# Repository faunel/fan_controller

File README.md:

English | [Українська](README.uk.md)

# PWM Fan Controller Board

A control board for regulating fan speed using PWM (Pulse-Width Modulation).

## Overview

This board is designed to control up to four fans based on temperature readings from up to four NTC thermistors.  
It is intended, in particular, for use with hybrid inverters and includes an inverter fan emulation mode.

- Total output current: up to **5 A**, sufficient with a large margin for typical fans
- Temperature sensor type: **NTC 10 kΩ**
- Up to **4 fans** supported
- Up to **4 temperature sensors** supported
- **4 fan speed levels** depending on temperature
- **1 additional default speed** (used when temperature is below the first level)

## Fan–Sensor Mapping

Fan control logic is configurable in the menu:

- Any sensor can control any fan or group of fans
- All combinations are allowed

Examples:

- One sensor controls all 4 fans
- Two sensors:  
  - Sensor 1 controls fans 1–2  
  - Sensor 2 controls fans 3–4
- One sensor controls a single fan, another sensor controls the remaining three, etc.

The main menu displays for each fan/sensor:

- Temperature
- Fan speed (RPM)
- Current speed level (step)

## Hybrid Inverter Integration

The board is designed to work with a hybrid inverter and supports an **inverter fan emulation mode**.

- If the configuration allows the fans to be stopped (note: not all fans support full stop),
  the inverter will **not** generate a “fan stopped” error.
- Emulation is implemented by generating pulses at **300 Hz** on the signal (yellow) wire
  of the fan connector where the inverter’s original fan would normally be connected.

This corresponds to **9000 RPM** of the fan:

- 2 pulses per revolution  
- Formula: `300 / 2 * 60 = 9000`

### Fan Fault Handling

If the configuration requires a fan to rotate but it does not (for example):

- the connector is unplugged,
- the fan is blocked by a foreign object,
- the fan is defective,

then the inverter will detect an error and shut down until the cause is eliminated.  
This behaviour is intentional to prevent inverter overheating.

## Firmware / Development

### Flashing the firmware

```bash
cargo flash --chip stm32f411ceu6 --release
```

### Build and run with active terminal output

```bash
cargo run --release
```

### Build and detach from terminal

```bash
cargo embed --release
```

### Convert to HEX file

```bash
cargo-objcopy target/thumbv7em-none-eabihf/release/two --release -- -O ihex two.hex
```

### Disassembly

```bash
cargo objdump --bin two --release -- --disassemble --no-show-raw-insn --print-imm-hex
```

### Start OpenOCD

```bash
openocd -f interface/stlink.cfg -f target/stm32f4x.cfg
```

### Check program size

```bash
cargo size --bin fan_controller --release -- -A
```

## Memory Layout

### Program memory (Flash, base address: `0x08000000`)

- `.vector_table` – interrupt vector table, usually at the beginning of memory, containing addresses of interrupt handlers
- `.text` – section with program machine code (instructions)
- `.rodata` – section for constant, read-only data

### RAM (base address: `0x20000000`)

- `.data` – global and static variables initialized to specific values
- `.bss` – global and static variables initialized to zero
- `.uninit` – variables that are not initialized at program start

### Sections not included in the final binary / not critical for runtime

- `.gnu.sgstubs` – may contain special GNU-specific stubs
- `.ARM.attributes` – ARM-architecture-specific attributes
- `.comment` – comments or metadata
- `.defmt` – data for formatted output (e.g., for the `defmt` library)

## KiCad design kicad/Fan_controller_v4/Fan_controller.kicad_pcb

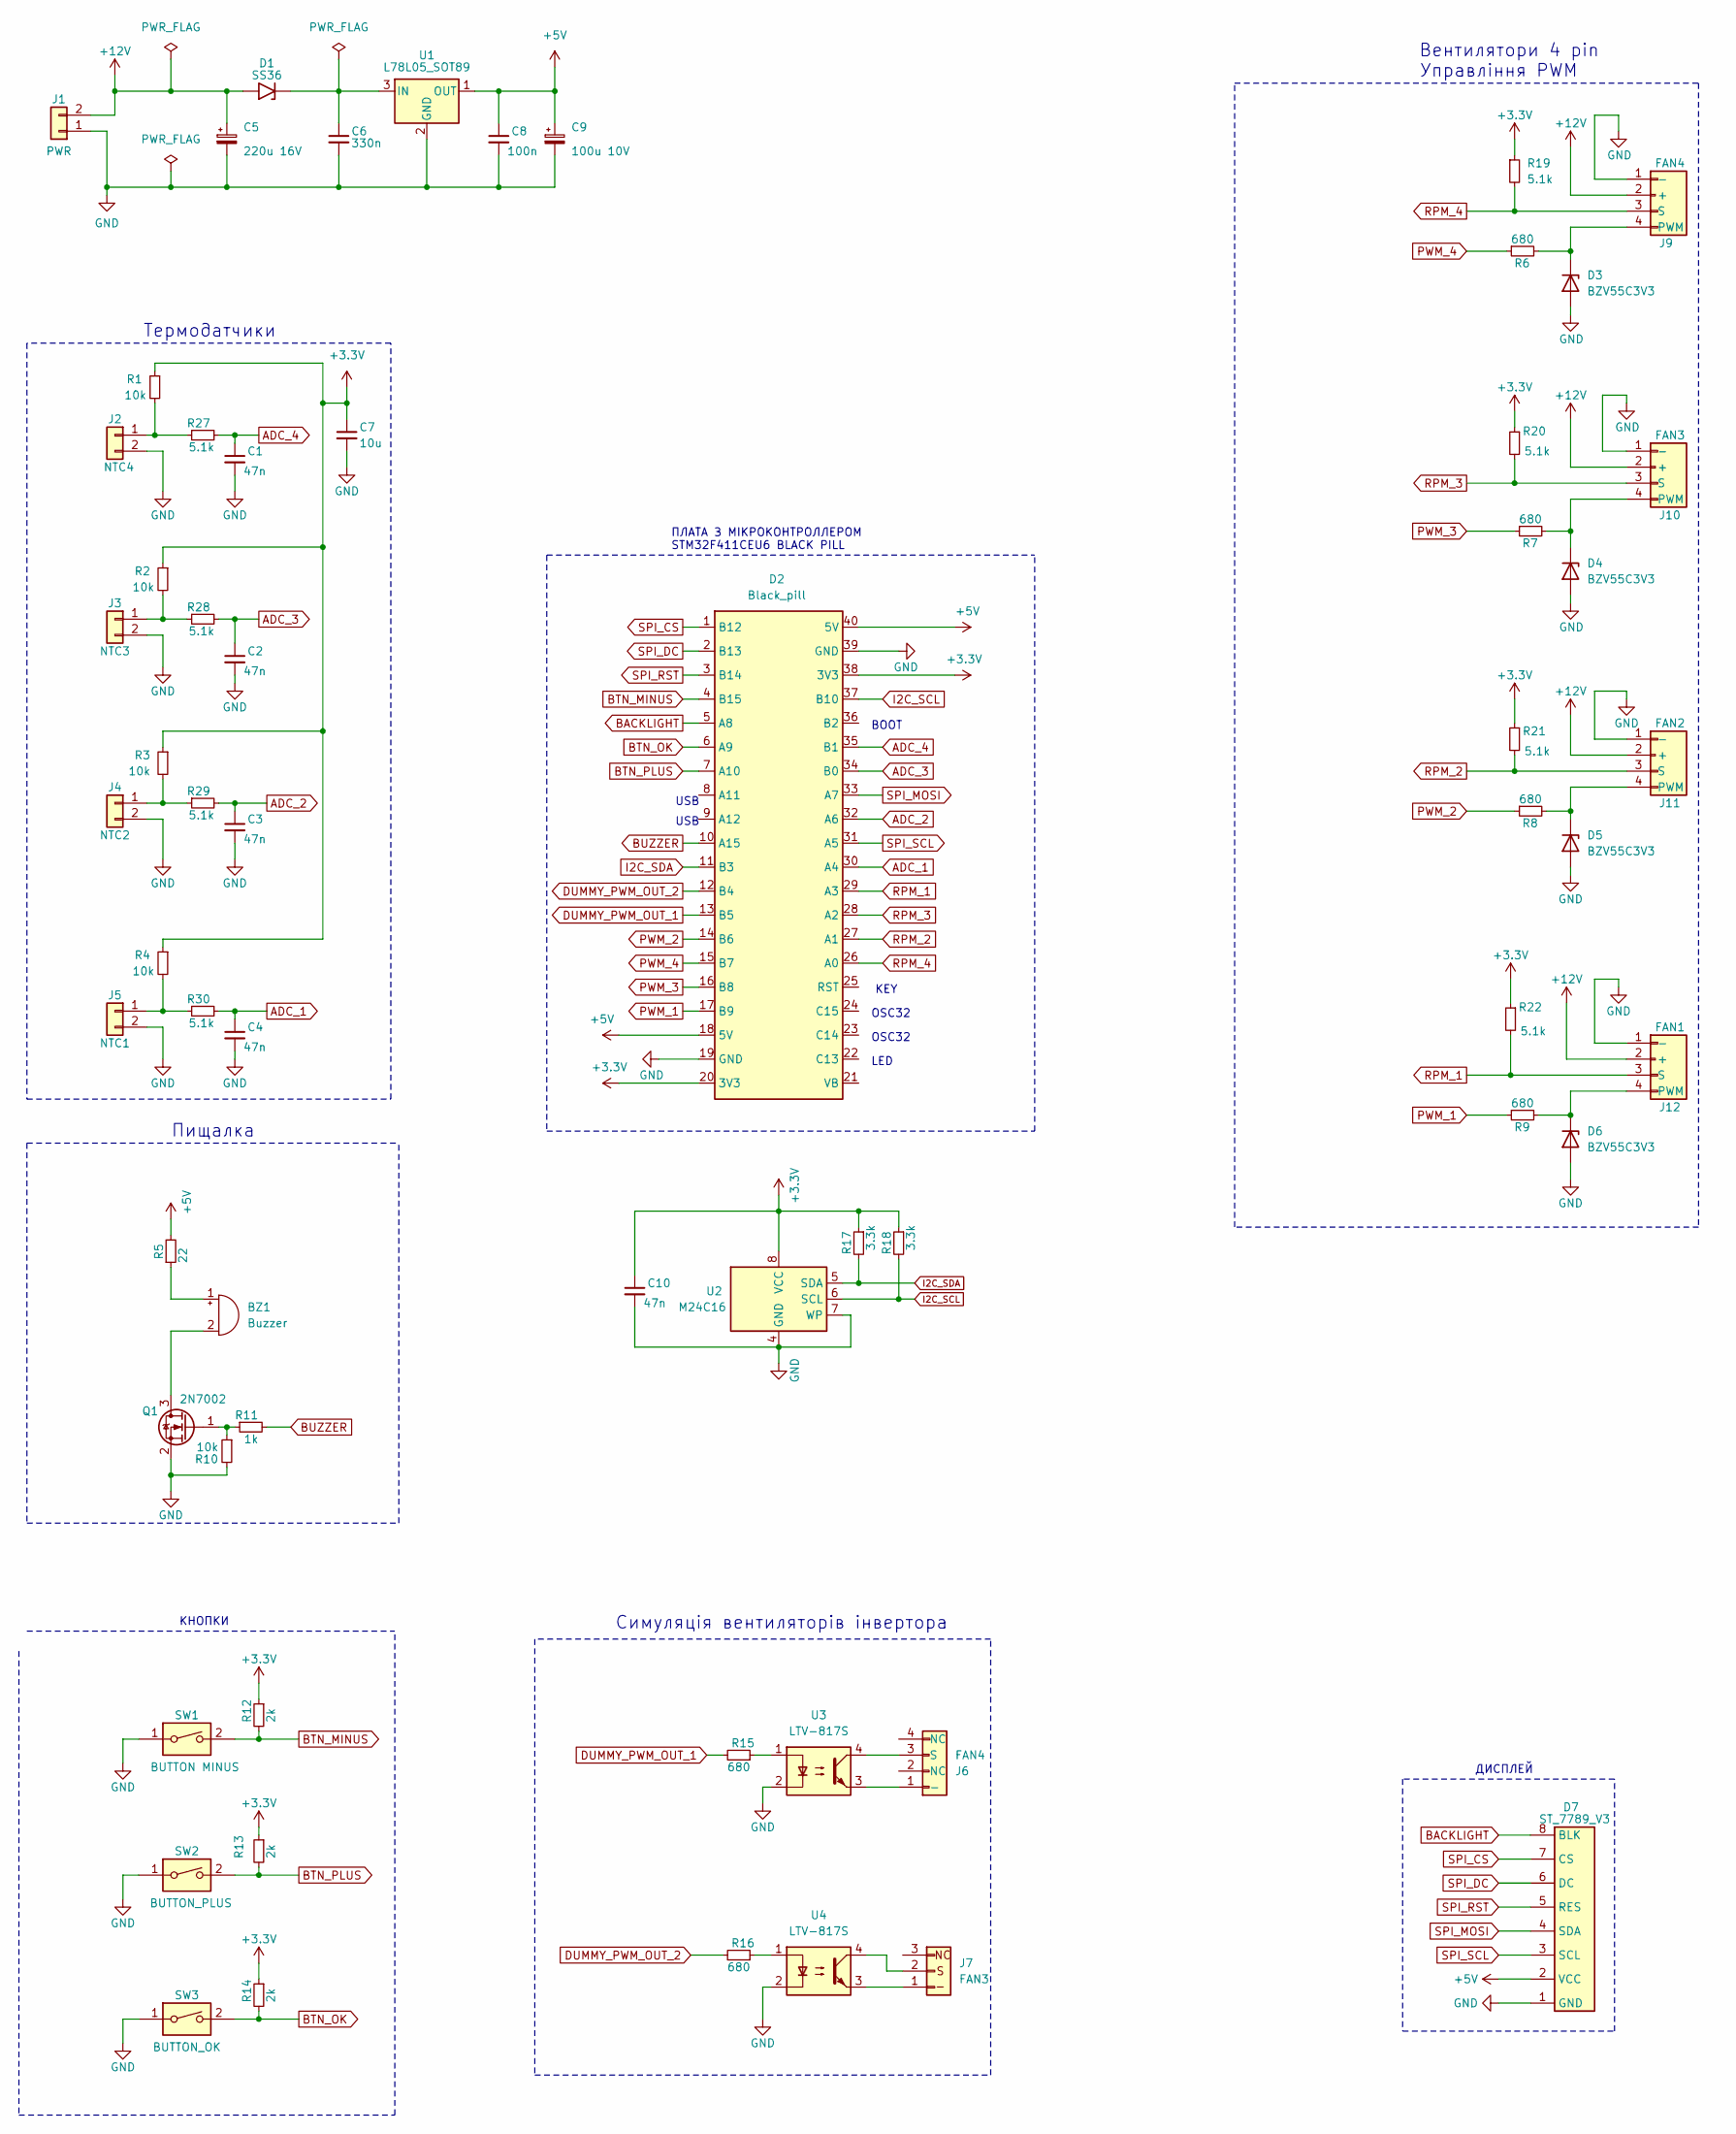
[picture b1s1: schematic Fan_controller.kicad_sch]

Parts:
BZ1: Buzzer; Buzzer_12x9.5RM7.6
C1, C2, C3, C4, C10: 47n; C_0805_2012Metric_Pad1.18x1.45mm_HandSolder
C5: 220u 16V; CP_Elec_6.3x7.7
C6: 330n; C_0805_2012Metric_Pad1.18x1.45mm_HandSolder
C7: 10u; C_0805_2012Metric_Pad1.18x1.45mm_HandSolder
C8: 100n; C_0805_2012Metric_Pad1.18x1.45mm_HandSolder
C9: 100u 10V; CP_Elec_5x5.4
D1: SS36; D_SMA-SMB_Universal_Handsoldering
D2: Black_pill
D3, D4, D5, D6: BZV55C3V3; D_SOD-123
D7: ST_7789_V3
J1: PWR; TerminalBlock_MetzConnect_Type094_RT03502HBLU_1x02_P5.00mm_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
J2: NTC4; JST_XH_B2B-XH-A_1x02_P2.50mm_Vertical
J3: NTC3; JST_XH_B2B-XH-A_1x02_P2.50mm_Vertical
J4: NTC2; JST_XH_B2B-XH-A_1x02_P2.50mm_Vertical
J5: NTC1; JST_XH_B2B-XH-A_1x02_P2.50mm_Vertical
J6: FAN4; JST_XH_B4B-XH-A_1x04_P2.50mm_Vertical
J7: FAN3; JST_XH_B3B-XH-A_1x03_P2.50mm_Vertical
J9: FAN4; FanPinHeader_1x04_P2.54mm_Vertical
J10: FAN3; FanPinHeader_1x04_P2.54mm_Vertical
J11: FAN2; FanPinHeader_1x04_P2.54mm_Vertical
J12: FAN1; FanPinHeader_1x04_P2.54mm_Vertical
Q1: 2N7002; SOT-23
R1, R2, R3, R4, R10: 10k; R_0805_2012Metric_Pad1.20x1.40mm_HandSolder
R5: 22; R_0805_2012Metric_Pad1.20x1.40mm_HandSolder
R6, R7, R8, R9, R15, R16: 680; R_0805_2012Metric_Pad1.20x1.40mm_HandSolder
R11: 1k; R_0805_2012Metric_Pad1.20x1.40mm_HandSolder
R12, R13, R14: 2k; R_0805_2012Metric_Pad1.20x1.40mm_HandSolder
R17, R18: 3.3k; R_0805_2012Metric_Pad1.20x1.40mm_HandSolder
R19, R20, R21, R22, R27, R28, R29, R30: 5.1k; R_0805_2012Metric_Pad1.20x1.40mm_HandSolder
SW1: BUTTON MINUS; SW_PUSH-12mm
SW2: BUTTON_PLUS; SW_PUSH-12mm
SW3: BUTTON_OK; SW_PUSH-12mm
U1: L78L05_SOT89; SOT-89-3
U2: M24C16; SOIC-8_3.9x4.9mm_P1.27mm
U3, U4: LTV-817S; SMDIP-4_W9.53mm

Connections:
+3.3V: C7.1, C10.1, D2.20 (3V3), D2.38 (3V3), R1.1, R2.1, R3.1, R4.1, R12.1, R13.1, R14.1, R17.1, R18.1, R19.1, R20.1, R21.1, R22.1, U2.8 (VCC)
+5V: C8.1, C9.1, D2.18 (5V), D2.40 (5V), D7.2 (VCC), R5.2, U1.1 (OUT)
+12V: C5.1, D1.2 (A2), J1.2, J9.2 (+), J10.2 (+), J11.2 (+), J12.2 (+)
ADC_1: C4.1, D2.30 (A4), R30.2
ADC_2: C3.1, D2.32 (A6), R29.2
ADC_3: C2.1, D2.34 (B0), R28.2
ADC_4: C1.1, D2.35 (B1), R27.2
BACKLIGHT: D2.5 (A8), D7.8 (BLK)
BTN_MINUS: D2.4 (B15), R12.2, SW1.2
BTN_OK: D2.6 (A9), R14.2, SW3.2
BTN_PLUS: D2.7 (A10), R13.2, SW2.2
BUZZER: D2.10 (A15), R11.2
DUMMY_PWM_OUT_1: D2.13 (B5), R15.2
DUMMY_PWM_OUT_2: D2.12 (B4), R16.2
GND: C1.2, C2.2, C3.2, C4.2, C5.2, C6.2, C7.2, C8.2, C9.2, C10.2, D2.19 (GND), D2.39 (GND), D3.2 (A), D4.2 (A), D5.2 (A), D6.2 (A), D7.1 (GND), J1.1, J2.2, J3.2, J4.2, J5.2, J9.1 (-), J10.1 (-), J11.1 (-), J12.1 (-), Q1.2 (S), R10.2, SW1.1, SW2.1, SW3.1, U1.2 (GND), U2.4 (GND), U2.7 (WP), U3.2, U4.2
I2C_SCL: D2.37 (B10), R18.2, U2.6 (SCL)
I2C_SDA: D2.11 (B3), R17.2, U2.5 (SDA)
unnamed: BZ1.2 (+), Q1.3 (D)
unnamed: BZ1.1 (-), R5.1
unnamed: C6.1, D1.1 (A1), U1.3 (IN)
unnamed: D3.1 (K), J9.4 (PWM), R6.2
unnamed: D4.1 (K), J10.4 (PWM), R7.2
unnamed: D5.1 (K), J11.4 (PWM), R8.2
unnamed: D6.1 (K), J12.4 (PWM), R9.2
unnamed: J2.1, R1.2, R27.1
unnamed: J3.1, R2.2, R28.1
unnamed: J4.1, R3.2, R29.1
unnamed: J5.1, R4.2, R30.1
unnamed: J6.1 (-), U3.3
unnamed: J6.3 (S), U3.4
unnamed: J7.1 (NC), U4.3
unnamed: J7.2, U4.4
unnamed: Q1.1 (G), R10.1, R11.1
unnamed: R15.1, U3.1
unnamed: R16.1, U4.1
PWM_1: D2.17 (B9), R9.1
PWM_2: D2.14 (B6), R8.1
PWM_3: D2.16 (B8), R7.1
PWM_4: D2.15 (B7), R6.1
RPM_1: D2.29 (A3), J12.3 (S), R22.2
RPM_2: D2.27 (A1), J11.3 (S), R21.2
RPM_3: D2.28 (A2), J10.3 (S), R20.2
RPM_4: D2.26 (A0), J9.3 (S), R19.2
SPI_CS: D2.1 (B12), D7.7 (CS)
SPI_DC: D2.2 (B13), D7.6 (DC)
SPI_MOSI: D2.33 (A7), D7.4 (SDA)
SPI_RST: D2.3 (B14), D7.5 (RES)
SPI_SCL: D2.31 (A5), D7.3 (SCL)

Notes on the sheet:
OSC32
ДИСПЛЕЙ
USB
КНОПКИ
ПЛАТА З МІКРОКОНТРОЛЛЕРОМ STM32F411CEU6 BLACK PILL
KEY
LED
Пищалка
Вентилятори 4 pin Управління PWM
BOOT
Симуляція вентиляторів інвертора
Термодатчики

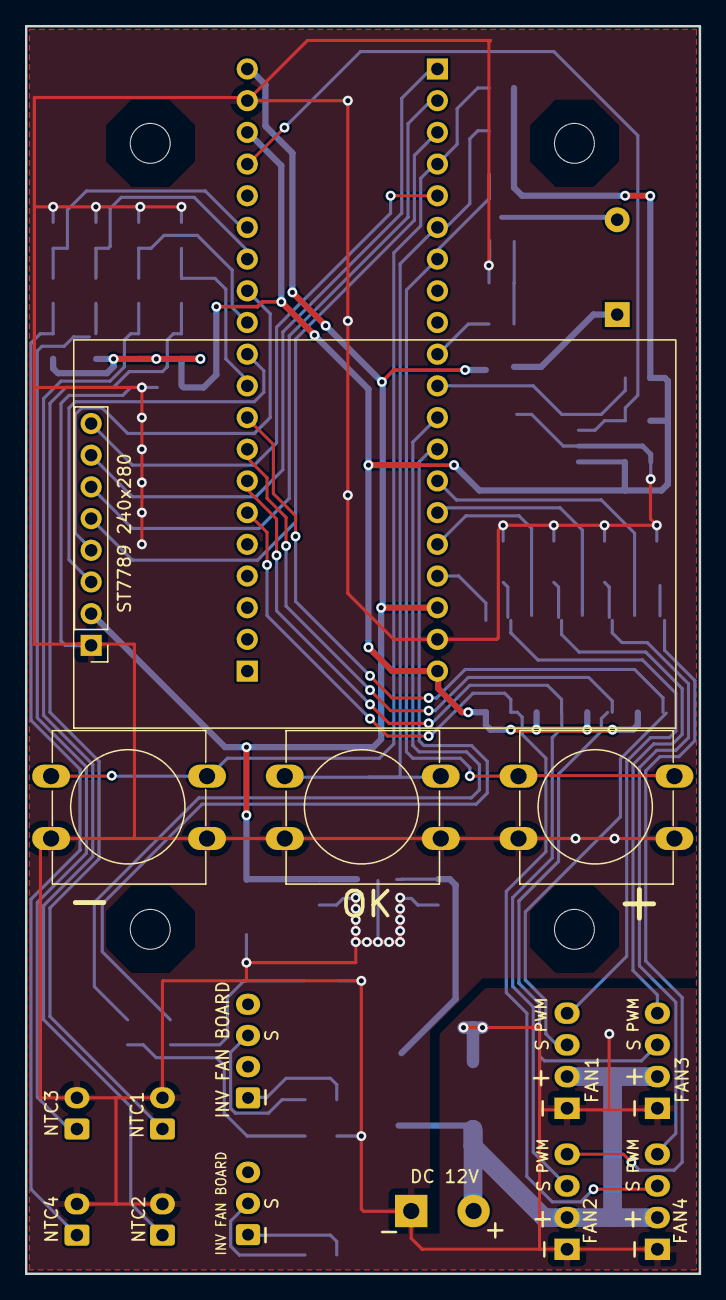
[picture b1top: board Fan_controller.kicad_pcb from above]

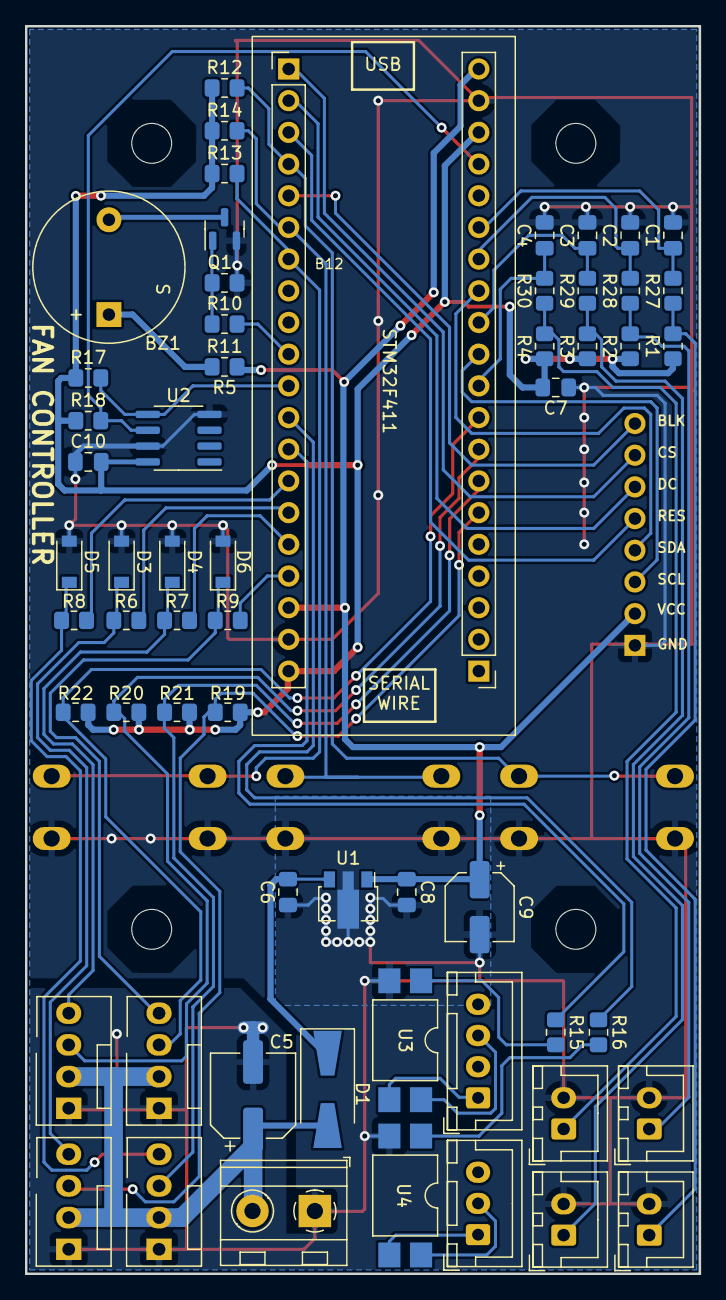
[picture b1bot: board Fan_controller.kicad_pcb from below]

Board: 2 copper layers, 54.0 x 100.0 mm, 63 parts (59 on the bottom side), 48 nets.

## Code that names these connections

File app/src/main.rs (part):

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        let sda_pin = Input::new(gpiob.pb3, Pull::Up);

        // Button pin config
        let btn_minus_pin = Input::new(gpiob.pb15, Pull::Up);
        let btn_ok_pin: Pin<'A', 9> = Input::new(gpioa.pa9, Pull::Up);
        let btn_plus_pin = Input::new(gpioa.pa10, Pull::Up);

        // Button async wrapper
        let btn_minus_async = WaitPin::new(btn_minus_pin);
        let mut btn_ok_async: WaitPin<Pin<'A', 9>> = WaitPin::new(btn_ok_pin);
        let btn_plus_async = WaitPin::new(btn_plus_pin);

        // Buzzer pin
        let _buzzer_pin: Pin<'A', 15, Output> = Output::new(gpioa.pa15, PinState::Low);

        // Backlight pin
        let backlight_pin = gpioa.pa8;

        // Fan PWM output pin
        let fan1_pwm_pin = gpiob.pb9;
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        // TIM1. For backlight. PWM output config
        let timer = Timer::new(dp.TIM1, &clocks);
        let (_, (ch1, ..)) = timer.pwm_hz(20.kHz());
        let mut bl_tim: timer::PwmChannel<TIM1, 0> = ch1.with(backlight_pin);
        bl_tim.set_duty(50);
        bl_tim.enable();

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        loop {
            let select = select3(btn_minus.update(), btn_ok.update(), btn_plus.update()).await;

            let is_pressed_minus_plus = btn_minus.is_pin_pressed() && btn_plus.is_pin_pressed();
            if is_pressed_minus_plus {
                Mono::delay(500.millis()).await;
                if is_pressed_minus_plus {
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
                                if item == 1 {
                                    if settings.backlight.data > 0 && !prev_pressed_minus_plus {
                                        settings.backlight.data -= 1;
                                    }
                                } else if settings.ntc_no[item - 2].data > 1 {
                                    settings.ntc_no[item - 2].data -= 1;
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                            Menu::Main => {}
                            Menu::Settings => {
                                if settings.backlight.data > 0 {
                                    settings.backlight.data -= 1;
                                }
                            }
                        },
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
                                if item == 1 {
                                    if settings.backlight.data < 10 && !prev_pressed_minus_plus {
                                        settings.backlight.data += 1
                                    }
                                } else if settings.ntc_no[item - 2].data < 4 {
                                    settings.ntc_no[item - 2].data += 1;
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                            Menu::Main => {}
                            Menu::Settings => {
                                if settings.backlight.data < 10 {
                                    settings.backlight.data += 1;
                                }
                            }
                        },
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
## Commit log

2024-09-07 alpha1
2024-09-14 beta1
2024-09-15 beta2
2024-09-15 beta3
2024-09-15 beta4
2024-09-15 beta5
2024-09-15 v.0.1
2024-09-16 v.0.1.1
2024-09-16 v.0.1.2
2024-09-16 v.0.1.3
2024-09-16 v.0.1.4
2024-09-20 v.0.2 (add Rc Rwlock)
2024-10-14 v.0.2
2025-11-11 add kicad project
2025-11-11 fix readme
2025-11-11 edit readme
2025-11-11 edit reame
